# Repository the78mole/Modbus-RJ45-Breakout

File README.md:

# Modbus-RJ45-Breakout
A breakout board for Dual-ModBus-over-Twisted-Pair (RJ45) with isolated converters option

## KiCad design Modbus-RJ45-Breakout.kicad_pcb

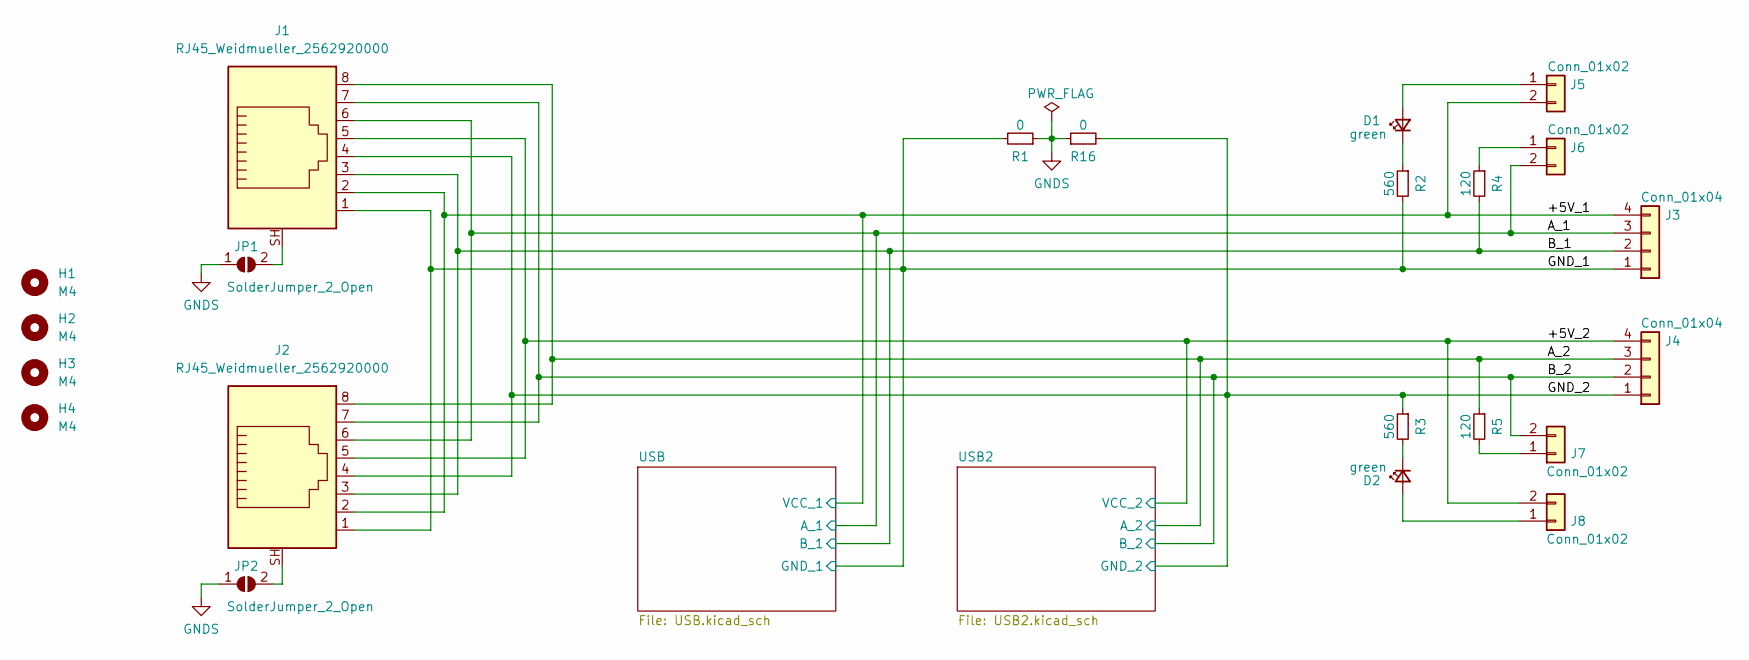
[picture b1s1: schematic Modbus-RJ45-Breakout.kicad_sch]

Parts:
D1, D2: green; LED_0603_1608Metric_Pad1.05x0.95mm_HandSolder
H1, H2, H3, H4: M4; MountingHole_4.3mm_M4_DIN965
J1, J2: RJ45_Weidmueller_2562920000; RJ45_Weidmüller_2562920000_Horizontal
J3, J4: Conn_01x04; Wago_734-164_1x04_P3.50mm_Horizontal
J5, J6, J7, J8: Conn_01x02; PinHeader_1x02_P2.54mm_Vertical
JP1, JP2: SolderJumper_2_Open; SolderJumper-2_P1.3mm_Open_TrianglePad1.0x1.5mm
R1, R16: 0; R_1206_3216Metric_Pad1.30x1.75mm_HandSolder
R2, R3: 560; R_0603_1608Metric_Pad0.98x0.95mm_HandSolder
R4, R5: 120; R_0603_1608Metric_Pad0.98x0.95mm_HandSolder

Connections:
/+5V_1: J1.2, J2.2, J3.4, J5.2; also elsewhere on the board
/+5V_2: J1.5, J2.5, J4.4, J8.2; also elsewhere on the board
/A_1: J1.6, J2.6, J3.3, J6.2; also elsewhere on the board
/A_2: J1.8, J2.8, J4.3, R5.1; also elsewhere on the board
/B_1: J1.3, J2.3, J3.2, R4.2; also elsewhere on the board
/B_2: J1.7, J2.7, J4.2, J7.2; also elsewhere on the board
/GND_1: J1.1, J2.1, J3.1, R1.2, R2.2; also elsewhere on the board
/GND_2: J1.4, J2.4, J4.1, R3.1, R16.2; also elsewhere on the board
GNDS: JP1.1 (A), JP2.1 (A), R1.1, R16.1
unnamed: D1.1 (K), R2.1
unnamed: D1.2 (A), J5.1
unnamed: D2.1 (K), R3.2
unnamed: D2.2 (A), J8.1
unnamed: J1.SH, JP1.2 (B)
unnamed: J2.SH, JP2.2 (B)
unnamed: J6.1, R4.1
unnamed: J7.1, R5.2

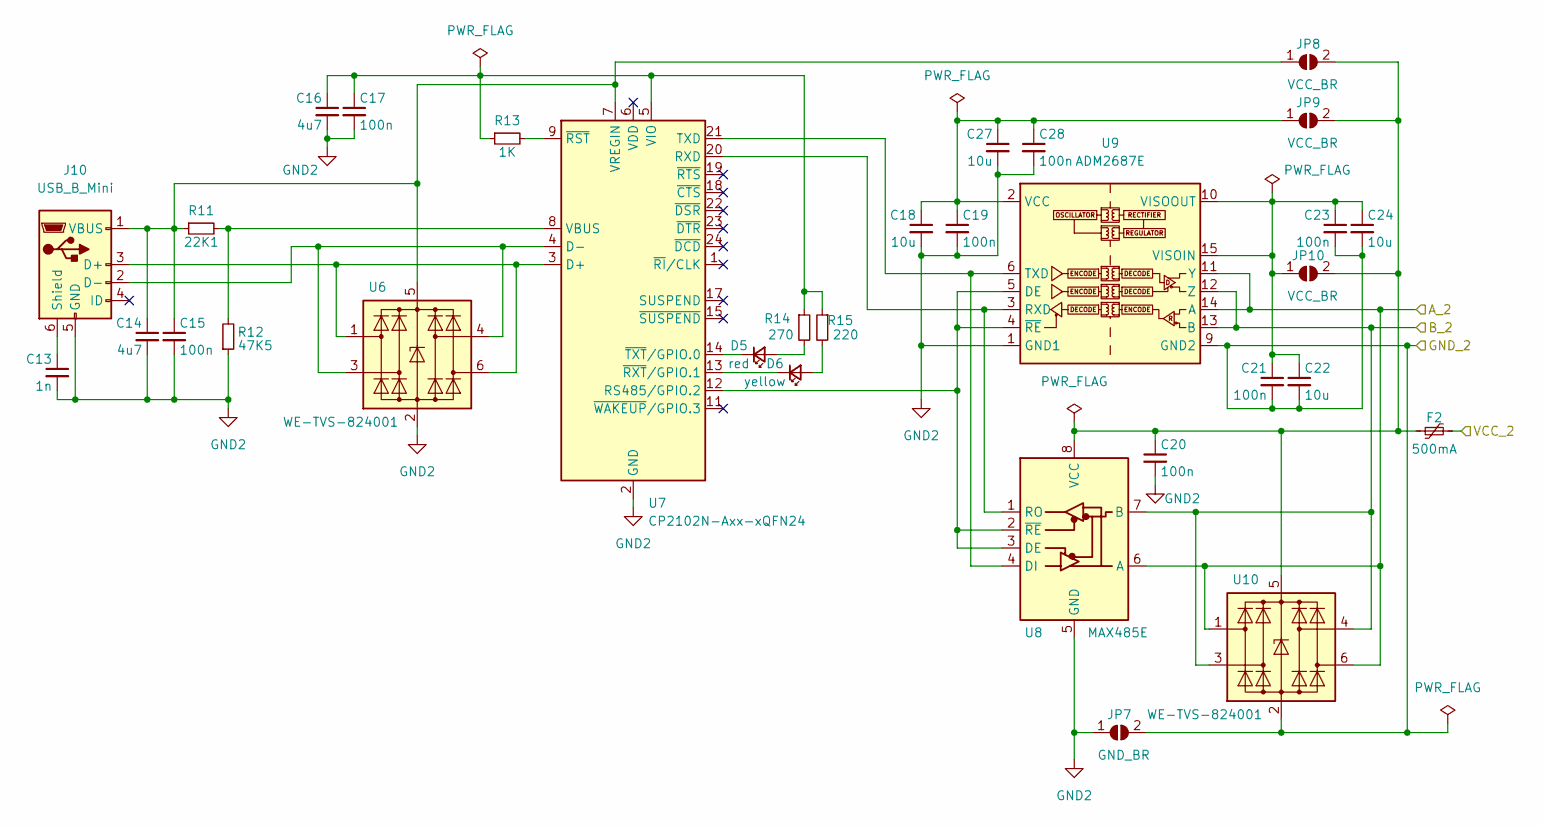
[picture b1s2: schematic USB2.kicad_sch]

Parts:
C13: 1n; C_1206_3216Metric_Pad1.33x1.80mm_HandSolder
C14, C16: 4u7; C_1206_3216Metric_Pad1.33x1.80mm_HandSolder
C15, C17, C19, C20, C21, C23, C28: 100n; C_0603_1608Metric_Pad1.08x0.95mm_HandSolder
C18, C22, C24, C27: 10u; C_1206_3216Metric_Pad1.33x1.80mm_HandSolder
D5: red; LED_0603_1608Metric_Pad1.05x0.95mm_HandSolder
D6: yellow; LED_0603_1608Metric_Pad1.05x0.95mm_HandSolder
F2: 500mA; Fuse_1206_3216Metric_Pad1.42x1.75mm_HandSolder
J10: USB_B_Mini; USB_Mini-B_Wuerth_65100516121_Horizontal
JP7: GND_BR; SolderJumper-2_P1.3mm_Open_TrianglePad1.0x1.5mm
JP8, JP9, JP10: VCC_BR; SolderJumper-2_P1.3mm_Open_TrianglePad1.0x1.5mm
R11: 22K1; R_0603_1608Metric_Pad0.98x0.95mm_HandSolder
R12: 47K5; R_0603_1608Metric_Pad0.98x0.95mm_HandSolder
R13: 1K; R_0603_1608Metric_Pad0.98x0.95mm_HandSolder
R14: 270; R_0603_1608Metric_Pad0.98x0.95mm_HandSolder
R15: 220; R_0603_1608Metric_Pad0.98x0.95mm_HandSolder
U6, U10: WE-TVS-824001; SOT-23-6
U7: CP2102N-Axx-xQFN24; QFN-24-1EP_4x4mm_P0.5mm_EP2.6x2.6mm
U8: MAX485E; SO-8_3.9x4.9mm_P1.27mm
U9: ADM2687E; SOIC-16W_7.5x12.8mm_P1.27mm

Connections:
/+5V_2: F2.2; also elsewhere on the board
/A_2: U8.6 (A), U9.11 (Y), U9.14 (A), U10.1 (I/O1), U10.6 (I/O4); also elsewhere on the board
/B_2: U8.7 (B), U9.12 (Z), U9.13 (B), U10.3 (I/O2), U10.4 (I/O3); also elsewhere on the board
/GND_2: C21.2, C22.2, C23.2, C24.2, JP7.2 (B), U9.9 (GND2), U9.16 (GND2), U10.2 (GND); also elsewhere on the board
GND2: C13.2, C14.2, C15.2, C16.2, C17.2, C18.2, C19.2, C20.2, C27.2, C28.2, J10.5 (GND), JP7.1 (A), R12.1, U6.2 (GND), U7.2 (GND), U7.25 (GND), U8.5 (GND), U9.1 (GND1), U9.8 (GND1)
unnamed: C13.1, J10.6 (Shield)
unnamed: C14.1, C15.1, J10.1 (VBUS), JP8.1 (A), R11.1, U6.5 (VBUS), U7.7 (VREGIN)
unnamed: C16.1, C17.1, R13.1, R14.1, R15.1, U7.5 (VIO)
unnamed: C18.1, C19.1, C27.1, C28.1, JP9.1 (A), U9.2 (VCC), U9.7 (VCC)
unnamed: C20.1, F2.1, JP8.2 (B), JP9.2 (B), JP10.2 (B), U8.8 (VCC), U10.5 (VBUS)
unnamed: C21.1, C22.1, C23.1, C24.1, JP10.1 (A), U9.10 (VISOOUT), U9.15 (VISOIN)
unnamed: D5.1 (K), U7.14 (~TXT/GPIO.0)
unnamed: D5.2 (A), R14.2
unnamed: D6.1 (K), U7.13 (~RXT/GPIO.1)
unnamed: D6.2 (A), R15.2
unnamed: J10.2 (D-), U6.3 (I/O2), U6.4 (I/O3), U7.4 (D-)
unnamed: J10.3 (D+), U6.1 (I/O1), U6.6 (I/O4), U7.3 (D+)
unnamed: R11.2, R12.2, U7.8 (VBUS)
unnamed: R13.2, U7.9 (~RST)
unnamed: U7.12 (RS485/GPIO.2), U8.2 (~RE), U8.3 (DE), U9.4 (~RE), U9.5 (DE)
unnamed: U7.20 (RXD), U8.1 (RO), U9.3 (RXD)
unnamed: U7.21 (TXD), U8.4 (DI), U9.6 (TXD)

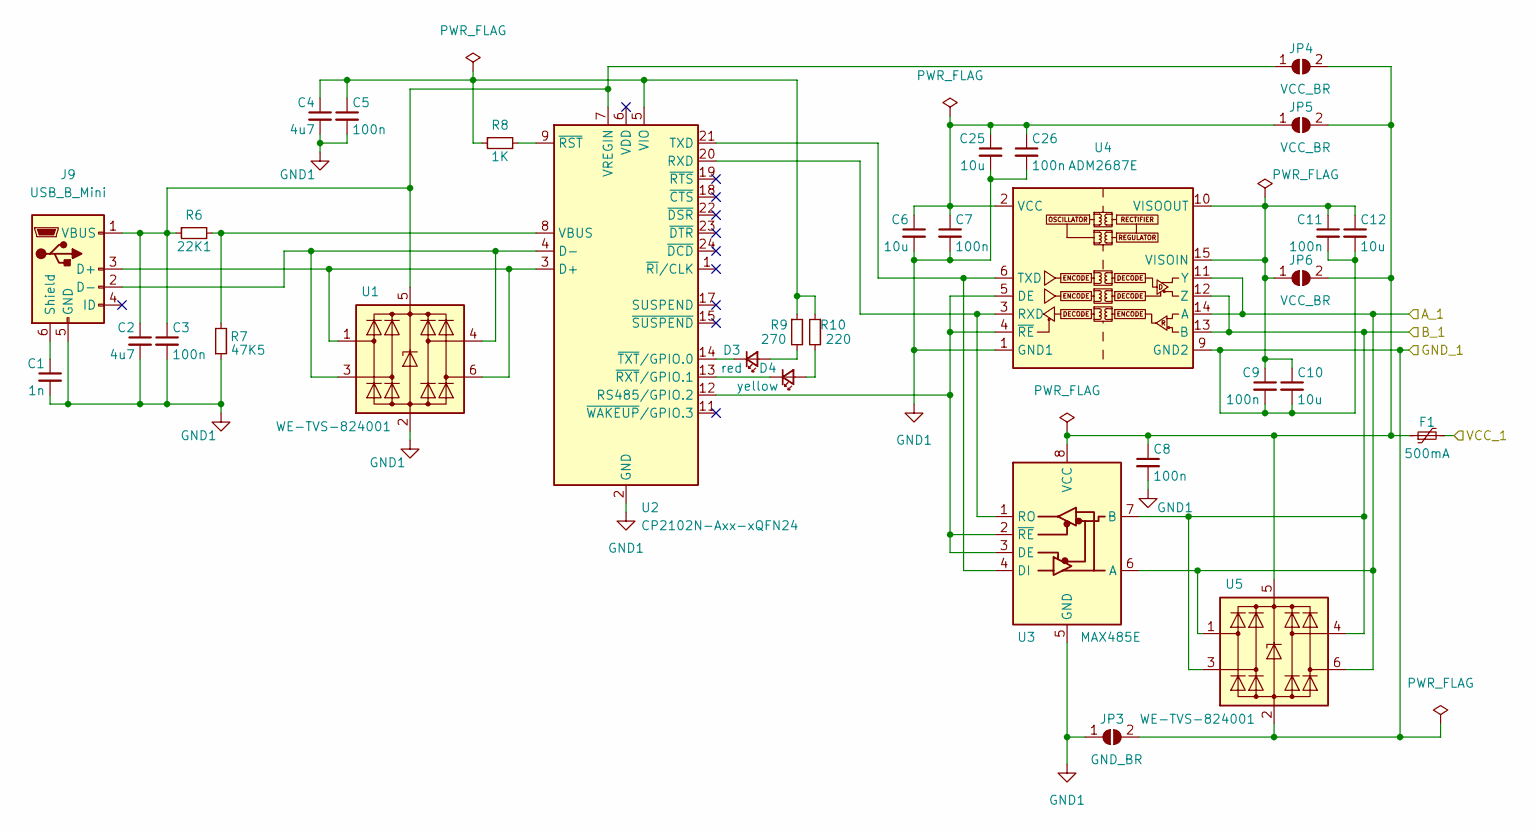
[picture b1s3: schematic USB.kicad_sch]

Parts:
C1: 1n; C_1206_3216Metric_Pad1.33x1.80mm_HandSolder
C2, C4: 4u7; C_1206_3216Metric_Pad1.33x1.80mm_HandSolder
C3, C5, C7, C8, C9, C11, C26: 100n; C_0603_1608Metric_Pad1.08x0.95mm_HandSolder
C6, C10, C12, C25: 10u; C_1206_3216Metric_Pad1.33x1.80mm_HandSolder
D3: red; LED_0603_1608Metric_Pad1.05x0.95mm_HandSolder
D4: yellow; LED_0603_1608Metric_Pad1.05x0.95mm_HandSolder
F1: 500mA; Fuse_1206_3216Metric_Pad1.42x1.75mm_HandSolder
J9: USB_B_Mini; USB_Mini-B_Wuerth_65100516121_Horizontal
JP3: GND_BR; SolderJumper-2_P1.3mm_Open_TrianglePad1.0x1.5mm
JP4, JP5, JP6: VCC_BR; SolderJumper-2_P1.3mm_Open_TrianglePad1.0x1.5mm
R6: 22K1; R_0603_1608Metric_Pad0.98x0.95mm_HandSolder
R7: 47K5; R_0603_1608Metric_Pad0.98x0.95mm_HandSolder
R8: 1K; R_0603_1608Metric_Pad0.98x0.95mm_HandSolder
R9: 270; R_0603_1608Metric_Pad0.98x0.95mm_HandSolder
R10: 220; R_0603_1608Metric_Pad0.98x0.95mm_HandSolder
U1, U5: WE-TVS-824001; SOT-23-6
U2: CP2102N-Axx-xQFN24; QFN-24-1EP_4x4mm_P0.5mm_EP2.6x2.6mm
U3: MAX485E; SO-8_3.9x4.9mm_P1.27mm
U4: ADM2687E; SOIC-16W_7.5x12.8mm_P1.27mm

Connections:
/+5V_1: F1.2; also elsewhere on the board
/A_1: U3.6 (A), U4.11 (Y), U4.14 (A), U5.1 (I/O1), U5.6 (I/O4); also elsewhere on the board
/B_1: U3.7 (B), U4.12 (Z), U4.13 (B), U5.3 (I/O2), U5.4 (I/O3); also elsewhere on the board
/GND_1: C9.2, C10.2, C11.2, C12.2, JP3.2 (B), U4.9 (GND2), U4.16 (GND2), U5.2 (GND); also elsewhere on the board
GND1: C1.2, C2.2, C3.2, C4.2, C5.2, C6.2, C7.2, C8.2, C25.2, C26.2, J9.5 (GND), JP3.1 (A), R7.1, U1.2 (GND), U2.2 (GND), U2.25 (GND), U3.5 (GND), U4.1 (GND1), U4.8 (GND1)
unnamed: C1.1, J9.6 (Shield)
unnamed: C2.1, C3.1, J9.1 (VBUS), JP4.1 (A), R6.1, U1.5 (VBUS), U2.7 (VREGIN)
unnamed: C4.1, C5.1, R8.1, R9.1, R10.1, U2.5 (VIO)
unnamed: C8.1, F1.1, JP4.2 (B), JP5.2 (B), JP6.2 (B), U3.8 (VCC), U5.5 (VBUS)
unnamed: C9.1, C10.1, C11.1, C12.1, JP6.1 (A), U4.10 (VISOOUT), U4.15 (VISOIN)
unnamed: C6.1, C7.1, C25.1, C26.1, JP5.1 (A), U4.2 (VCC), U4.7 (VCC)
unnamed: D3.1 (K), U2.14 (~TXT/GPIO.0)
unnamed: D3.2 (A), R9.2
unnamed: D4.1 (K), U2.13 (~RXT/GPIO.1)
unnamed: D4.2 (A), R10.2
unnamed: J9.2 (D-), U1.3 (I/O2), U1.4 (I/O3), U2.4 (D-)
unnamed: J9.3 (D+), U1.1 (I/O1), U1.6 (I/O4), U2.3 (D+)
unnamed: R6.2, R7.2, U2.8 (VBUS)
unnamed: R8.2, U2.9 (~RST)
unnamed: U2.12 (RS485/GPIO.2), U3.2 (~RE), U3.3 (DE), U4.4 (~RE), U4.5 (DE)
unnamed: U2.20 (RXD), U3.1 (RO), U4.3 (RXD)
unnamed: U2.21 (TXD), U3.4 (DI), U4.6 (TXD)

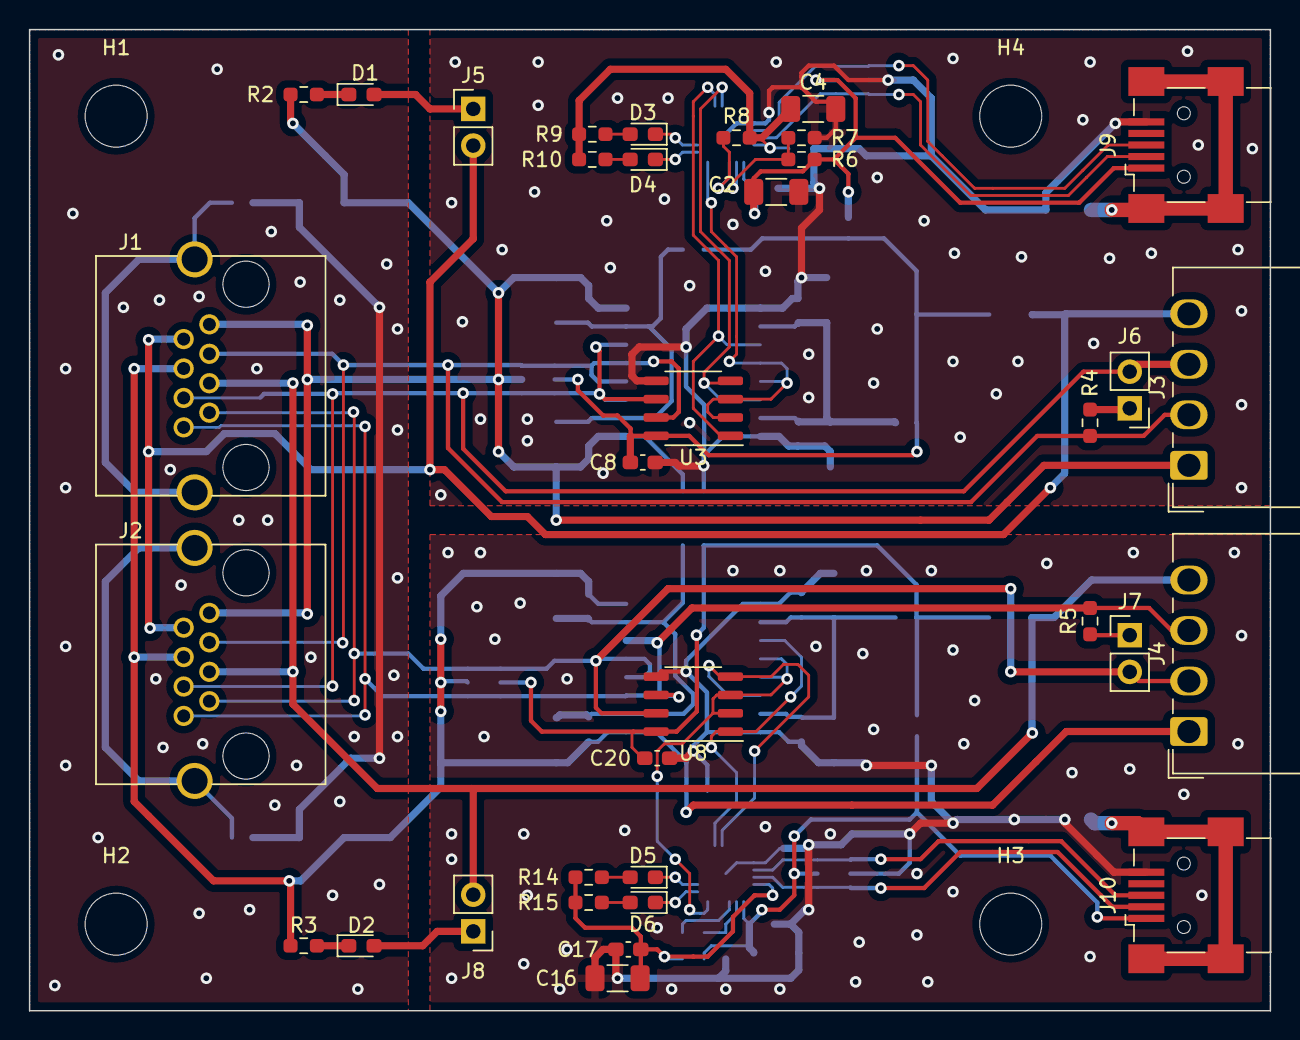
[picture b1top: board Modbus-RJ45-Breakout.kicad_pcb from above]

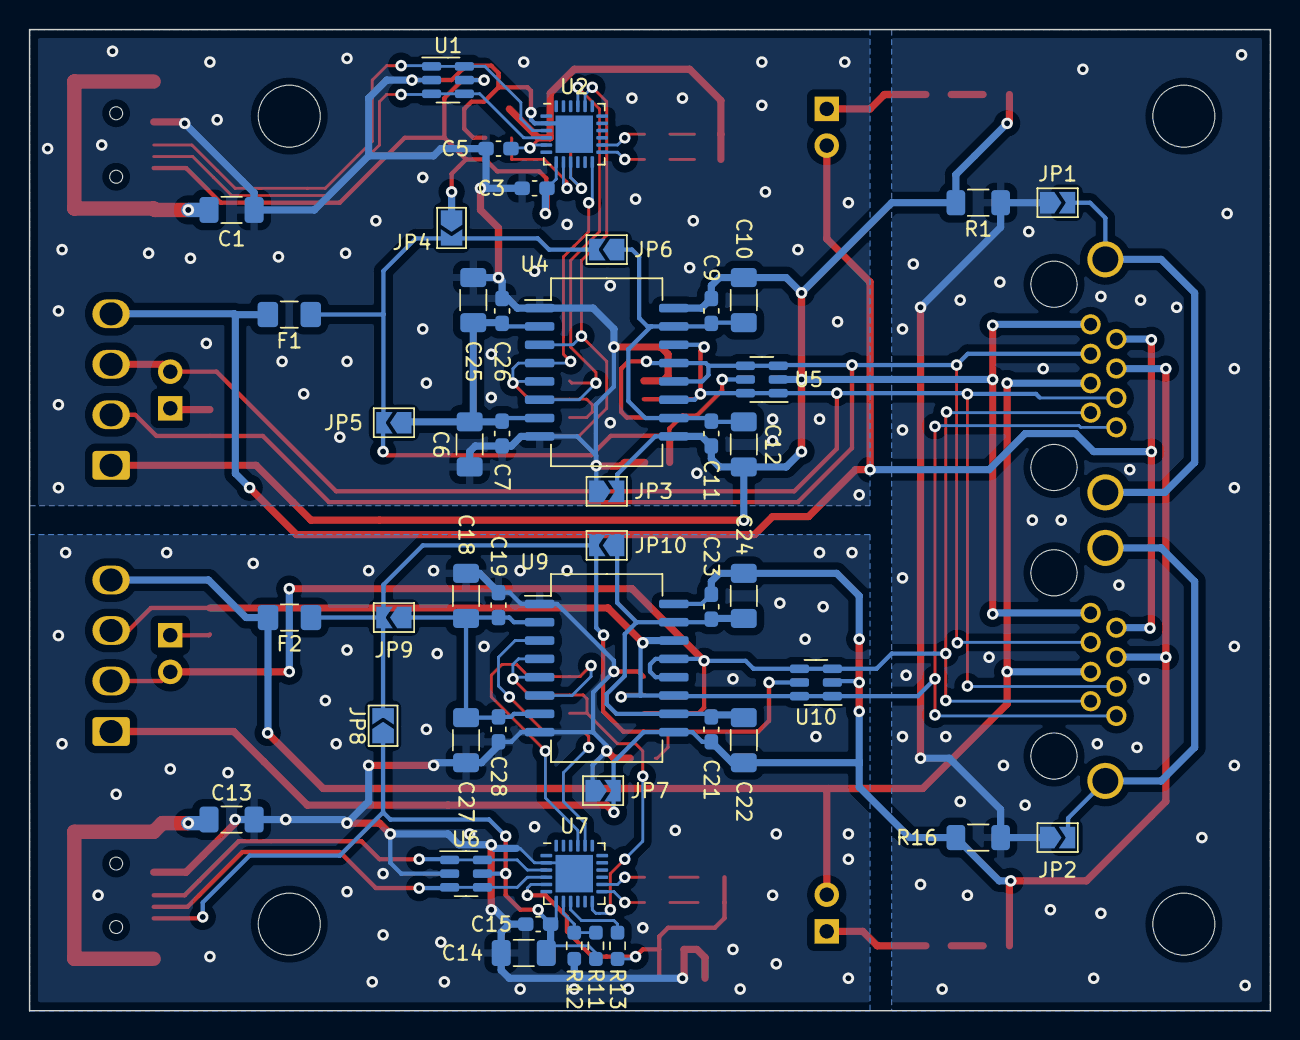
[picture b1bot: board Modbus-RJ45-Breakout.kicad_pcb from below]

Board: 2 copper layers, 86.0 x 68.0 mm, 86 parts (47 on the bottom side), 53 nets.

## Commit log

2023-04-24 Initial commit as ordered on PCBways
2023-04-24 Added the revision license and author information
2023-04-24 Added two render views
2023-04-26 Added dimensions to the PCB
2023-04-26 Added some 3D shapes -> Ethernet Connectors wrong
